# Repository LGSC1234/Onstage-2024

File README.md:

# Onstage-2024
Este repositorio tiene como objetivo demostrar el innovador trabajo del equipo, donde hemos integrado el emocionante tema de Taylor Swift dentro de nuestra performance.

-Robot Principal "Taylor Swift"

-Robot Secundario "Cartel Reconocimiento"

-Robot Secundario "Cartel Seguir Humano"

Para instalar el código de pyton se instalan las librerias mediante el requirements.txt y correr el archivo de main.py con permisos de administrador

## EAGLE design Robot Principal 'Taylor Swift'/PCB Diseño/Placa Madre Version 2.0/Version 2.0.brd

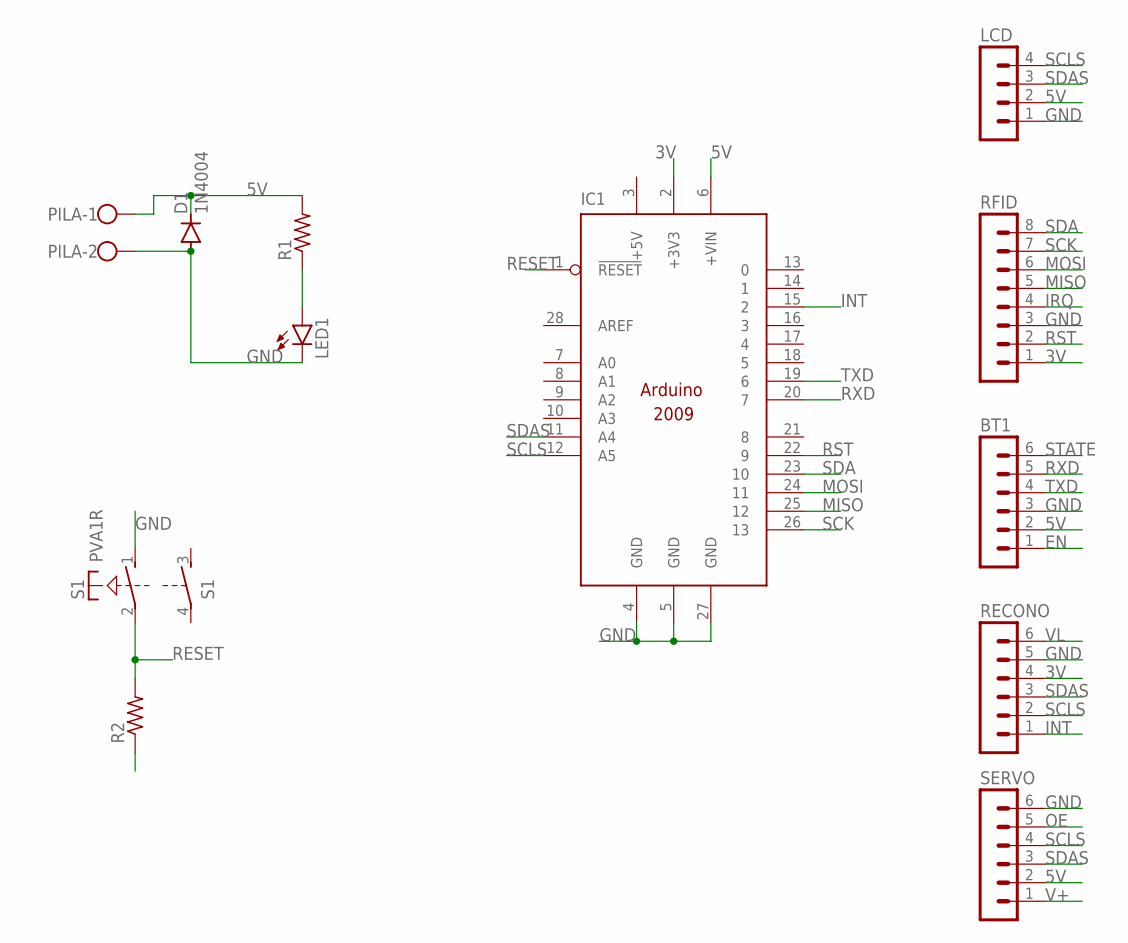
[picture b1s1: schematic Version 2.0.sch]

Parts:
BT1: MA06-1
D1: 1N4004; DO41-10
IC1: ARDUINO2009_10; ARDUINO2009
LCD: MA04-1
LED1: LED3MM
PILA: W237-102
R1, R2: R-US_0204/7; 0204/7
RECONO: MA06-1
RFID: MA08-1
S1: PVA1R
SERVO: MA06-1

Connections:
3V: IC1.2 (+3V3), RECONO.4, RFID.1
5V: BT1.2, D1.C, IC1.6 (+VIN), LCD.2, PILA.1, R1.2, R2.1, SERVO.2
+5V: IC1.3 (+5V)
EN: BT1.1
GND: BT1.3, D1.A, IC1.4 (GND), IC1.5 (GND), IC1.27 (GND), LCD.1, LED1.K (C), PILA.2, RECONO.5, RFID.3, S1.1 (S), SERVO.6
INT: IC1.15 (2), RECONO.1
IRQ: RFID.4
MISO: IC1.25 (12), RFID.5
MOSI: IC1.24 (11), RFID.6
unnamed: LED1.A, R1.1
OE: SERVO.5
RESET: IC1.1 (!RESET), R2.2, S1.2
RST: IC1.22 (9), RFID.2
RXD: BT1.5, IC1.20 (7)
SCK: IC1.26 (13), RFID.7
SCLS: IC1.12 (A5), LCD.4, RECONO.2, SERVO.4
SDA: IC1.23 (10), RFID.8
SDAS: IC1.11 (A4), LCD.3, RECONO.3, SERVO.3
STATE: BT1.6
TXD: BT1.4, IC1.19 (6)
V+: SERVO.1
VL: RECONO.6

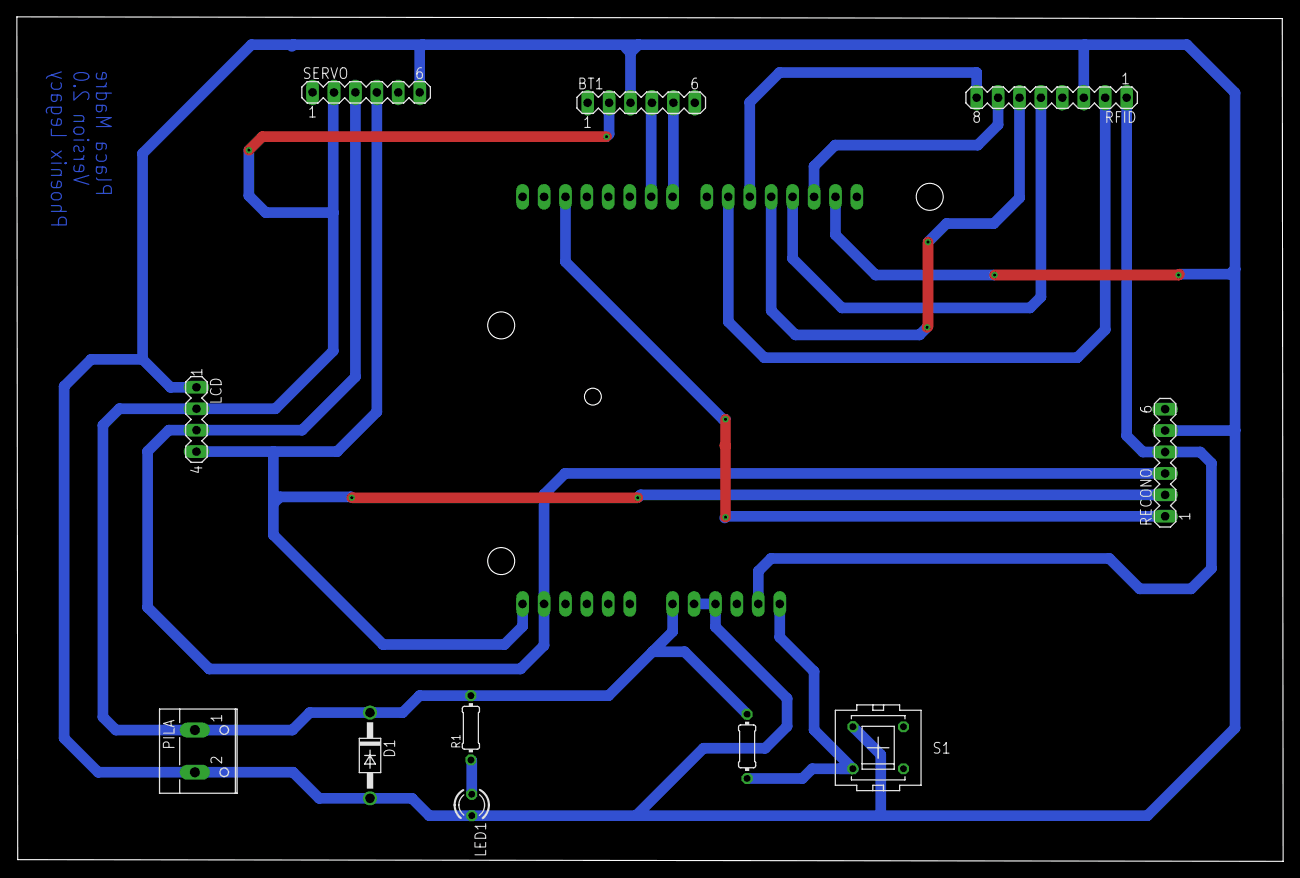
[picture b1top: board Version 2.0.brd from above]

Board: 2 copper layers, 150.1 x 100.1 mm, 12 parts (1 on the bottom side), 15 nets.

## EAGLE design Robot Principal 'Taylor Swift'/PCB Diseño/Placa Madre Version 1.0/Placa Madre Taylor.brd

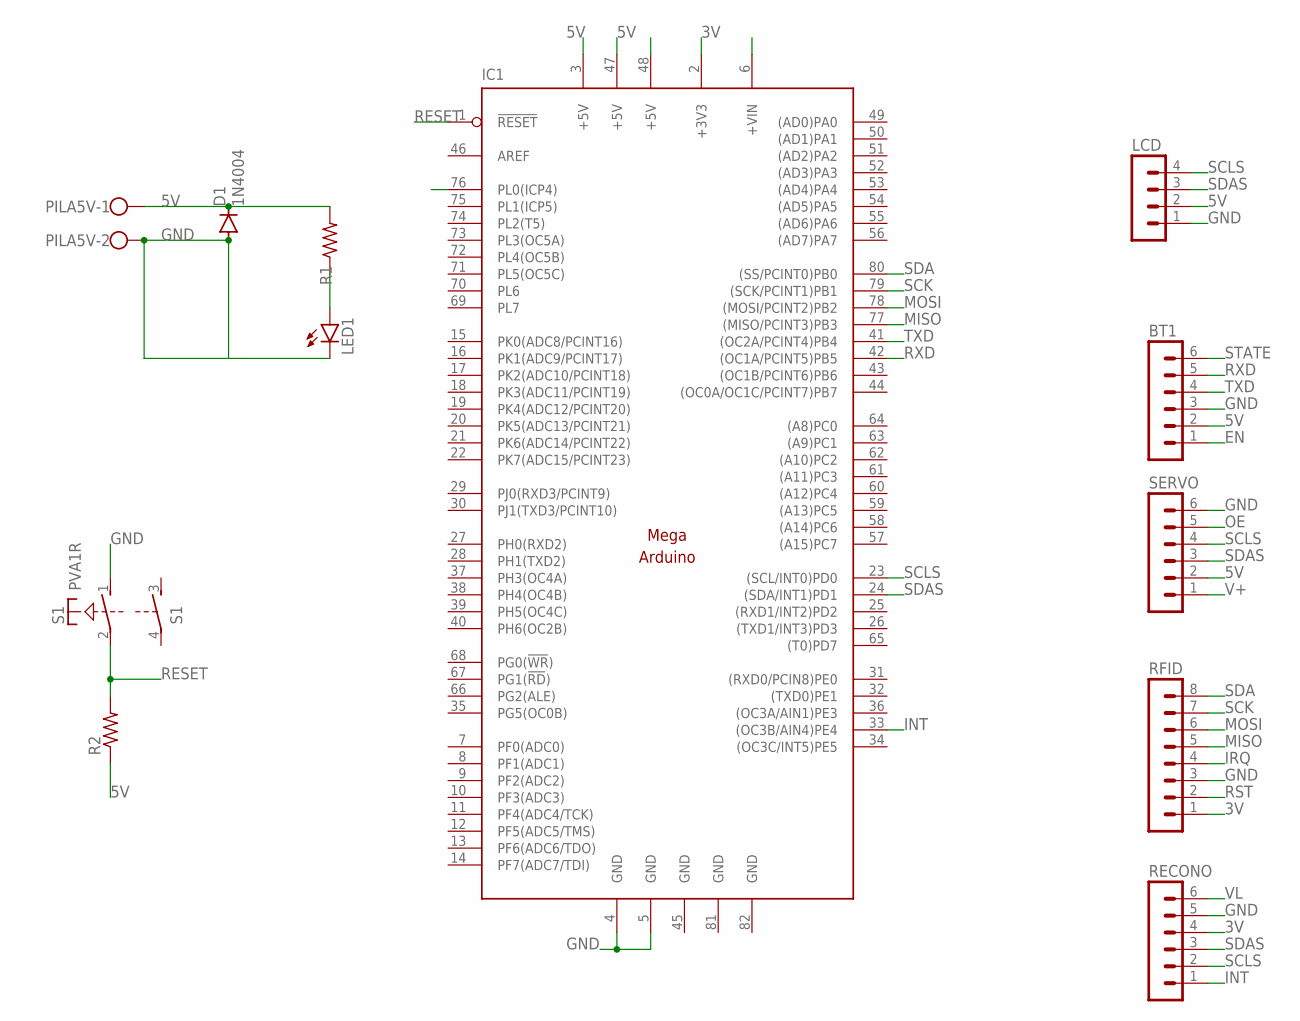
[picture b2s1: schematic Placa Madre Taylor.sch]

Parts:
BT1: MA06-1
D1: 1N4004; DO41-10
IC1: MEGAARDUINO_11; MEGA_ARDUINO_1
LCD: MA04-1
LED1: LED3MM
PILA5V: W237-102
R1: R-US_0204/7; 0204/7
R2: R-US_0207/10; 0207/10
RECONO: MA06-1
RFID: MA08-1
S1: PVA1R
SERVO: MA06-1

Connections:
3V: IC1.2 (+3V3), RECONO.4, RFID.1
5V: BT1.2, D1.C, IC1.3 (+5V), IC1.6 (+VIN), IC1.47 (+5V), LCD.2, PILA5V.1, R1.2, R2.1, SERVO.2
EN: BT1.1
GND: BT1.3, D1.A, IC1.4 (GND), IC1.5 (GND), IC1.45 (GND), IC1.81 (GND), IC1.82 (GND), LCD.1, LED1.K (C), PILA5V.2, RECONO.5, RFID.3, S1.1 (S), SERVO.6
INT: IC1.33 ((OC3B/AIN4)PE4), RECONO.1
IRQ: RFID.4
MISO: IC1.77 ((MISO/PCINT3)PB3), RFID.5
MOSI: IC1.78 ((MOSI/PCINT2)PB2), RFID.6
unnamed: LED1.A, R1.1
OE: SERVO.5
RESET: IC1.1 (!RESET), R2.2, S1.2
RST: IC1.76 (PL0(ICP4)), RFID.2
RXD: BT1.5, IC1.42 ((OC1A/PCINT5)PB5)
SCK: IC1.79 ((SCK/PCINT1)PB1), RFID.7
SCLS: IC1.23 ((SCL/INT0)PD0), LCD.4, RECONO.2, SERVO.4
SDA: IC1.80 ((SS/PCINT0)PB0), RFID.8
SDAS: IC1.24 ((SDA/INT1)PD1), LCD.3, RECONO.3, SERVO.3
STATE: BT1.6
TXD: BT1.4, IC1.41 ((OC2A/PCINT4)PB4)
V+: SERVO.1
VL: RECONO.6

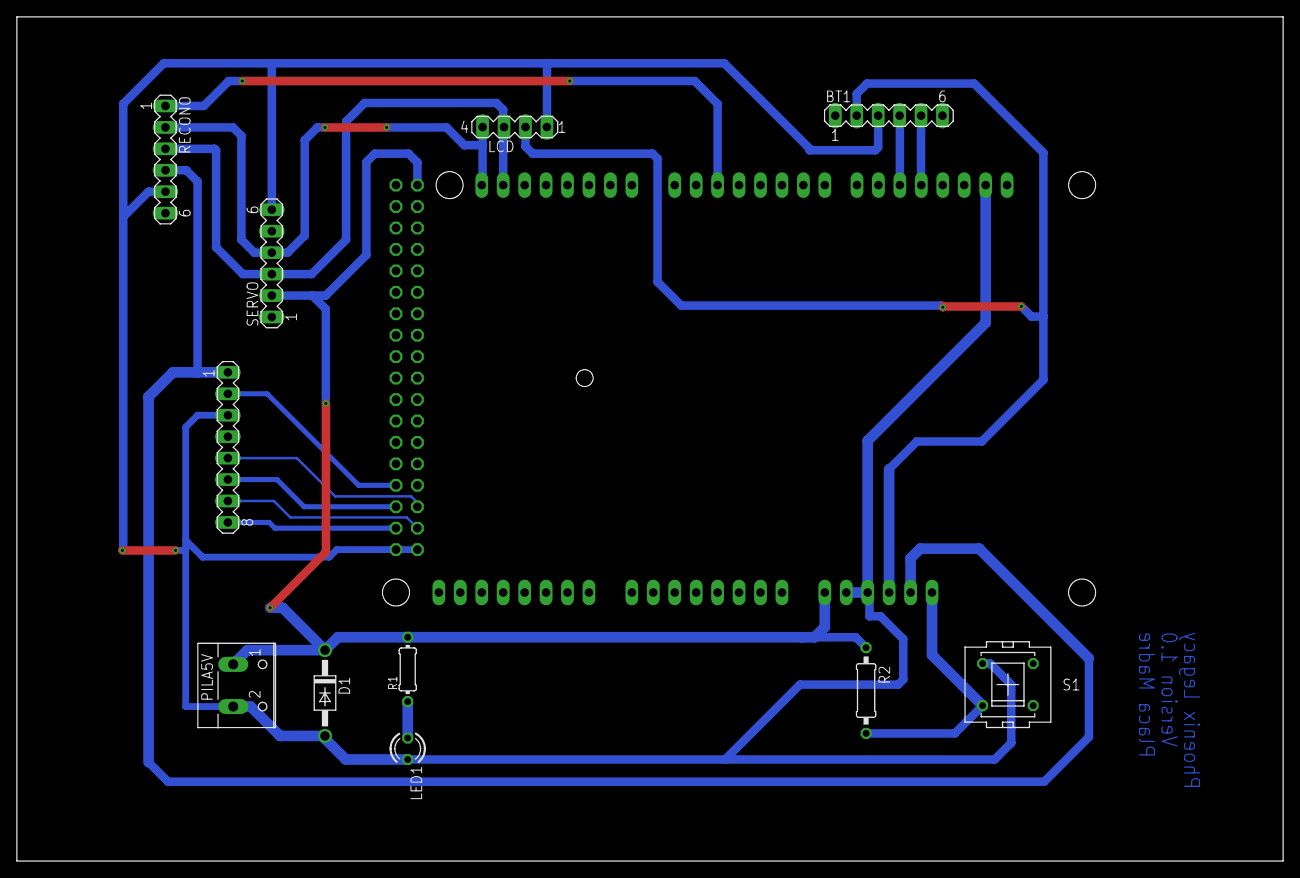
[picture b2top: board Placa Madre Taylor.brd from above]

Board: 2 copper layers, 150.0 x 100.0 mm, 12 parts (1 on the bottom side), 15 nets.

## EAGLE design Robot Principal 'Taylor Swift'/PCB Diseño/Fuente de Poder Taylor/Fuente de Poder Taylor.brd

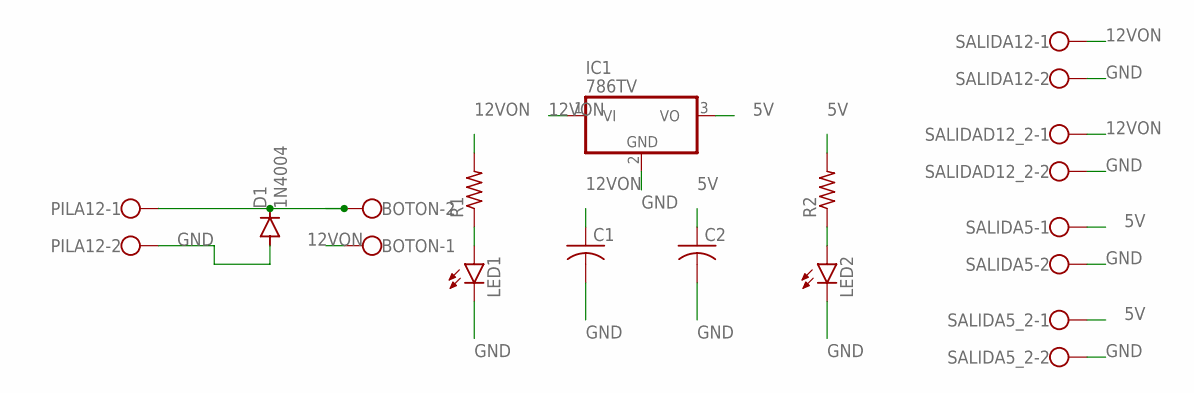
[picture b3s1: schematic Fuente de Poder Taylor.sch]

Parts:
BOTON: W237-102
C1, C2: C-US025-024X044; C025-024X044
D1: 1N4004; DO41-10
IC1: 786TV; TO220V
LED1, LED2: LED3MM
PILA12: W237-102
R1, R2: R-US_0204/7; 0204/7
SALIDA5, SALIDA5_2, SALIDA12: W237-102
SALIDAD12_2: W237-102

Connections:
5V: C2.1, IC1.3 (VO), R2.2, SALIDA5.1, SALIDA5_2.1
12VIN: BOTON.2, D1.C, PILA12.1
12VON: BOTON.1, C1.1, IC1.1 (VI), R1.2, SALIDA12.1, SALIDAD12_2.1
GND: C1.2, C2.2, D1.A, IC1.2 (GND), LED1.K (C), LED2.K (C), PILA12.2, SALIDA5.2, SALIDA5_2.2, SALIDA12.2, SALIDAD12_2.2
unnamed: LED1.A, R1.1
unnamed: LED2.A, R2.1

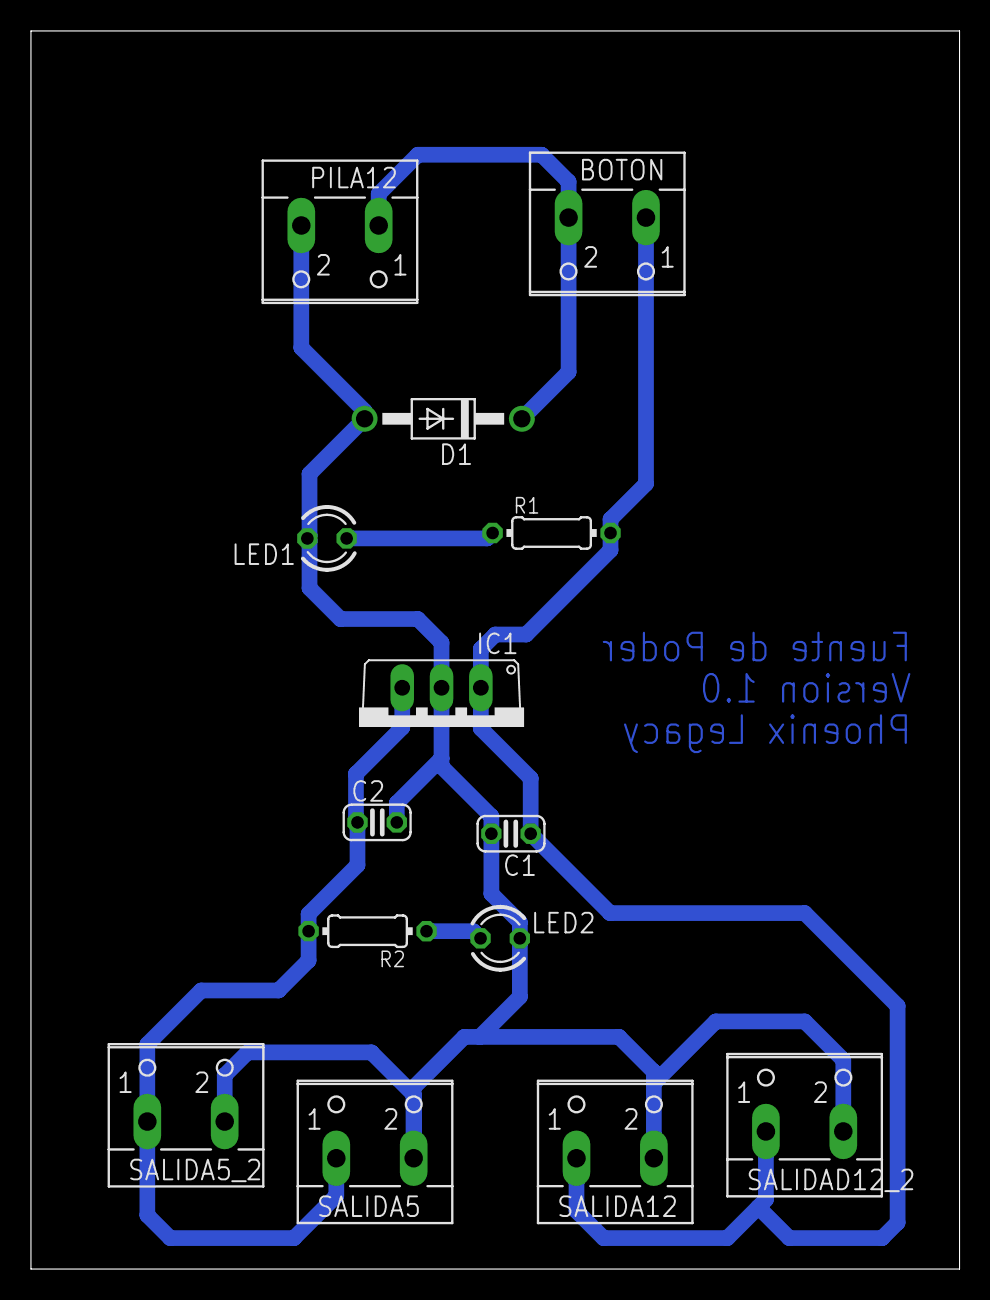
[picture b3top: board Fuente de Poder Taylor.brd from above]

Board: 2 copper layers, 60.0 x 80.0 mm, 14 parts (0 on the bottom side), 6 nets.

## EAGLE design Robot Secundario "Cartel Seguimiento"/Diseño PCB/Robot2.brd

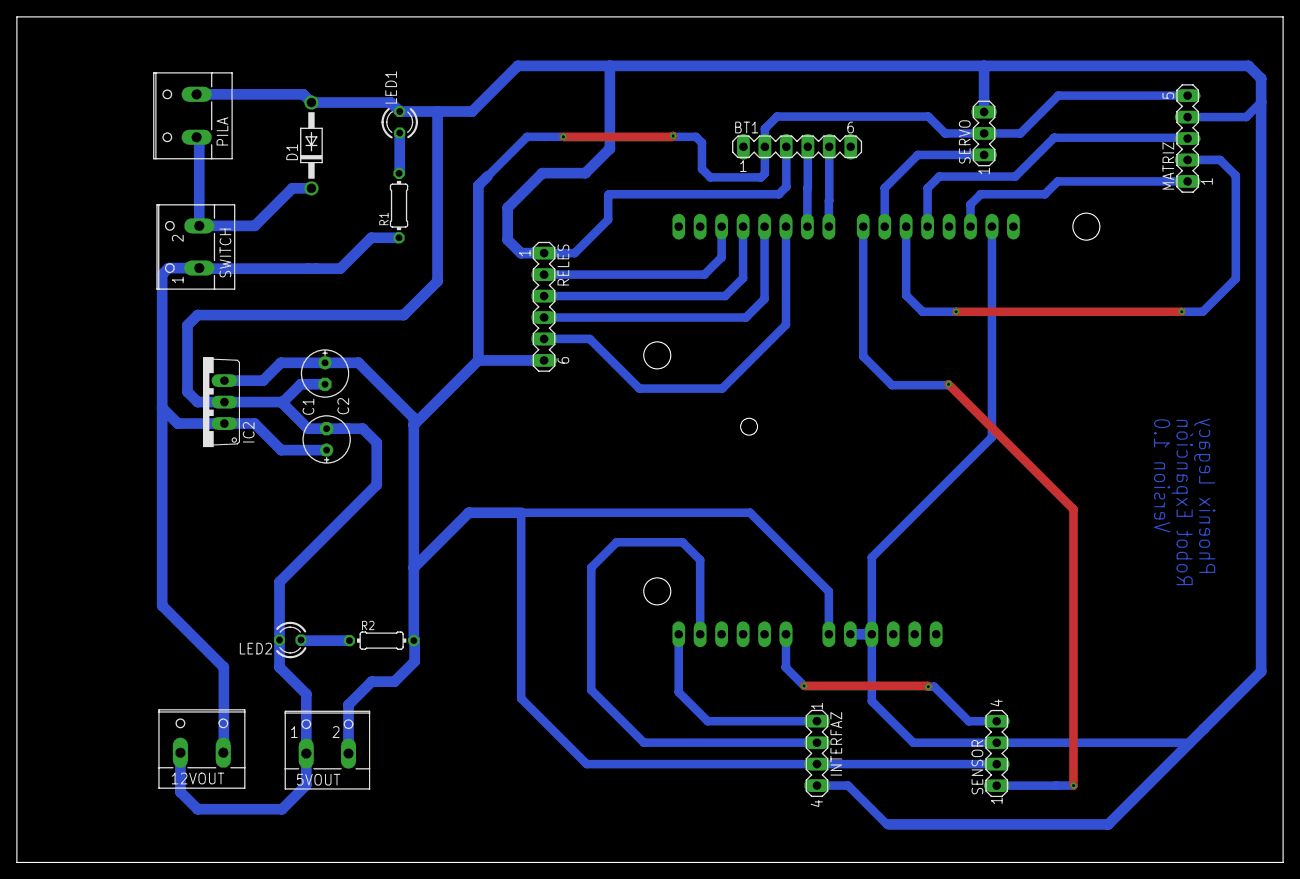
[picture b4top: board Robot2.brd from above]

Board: 2 copper layers, 149.9 x 100.1 mm, 19 parts (1 on the bottom side), 20 nets.

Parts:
5VOUT: W237-102
12VOUT: W237-132
BT1: MA06-1
C1, C2: E2,5-6E
D1: 1N4004; DO41-10
IC1: ARDUINO2009_1
IC2: 786TV; TO220V
INTERFAZ: MA04-1
LED1, LED2: LED3MM
MATRIZ: MA05-1
PILA: W237-132
R1, R2: 0204/7
RELES: MA06-1
SENSOR: MA04-1
SERVO: MA03-1
SWITCH: W237-102

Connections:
5V: 5VOUT.2, BT1.2, C2.+, IC1.6, IC2.3, INTERFAZ.3, MATRIZ.5, R2.2, RELES.6, SENSOR.2, SERVO.2
12VIN: D1.C, PILA.1, SWITCH.2
12VON: 12VOUT.2, C1.+, IC2.1, R1.1, SWITCH.1
A0: IC1.7, SENSOR.4
CLK: IC1.26, MATRIZ.1
CS: IC1.23, MATRIZ.2
D8: IC1.21, SENSOR.1
D9: IC1.22, SERVO.1
DIN: IC1.24, MATRIZ.3
GND: 5VOUT.1, 12VOUT.1, BT1.3, C1.-, C2.-, D1.A, IC1.4, IC1.5, IC1.27, IC2.2, INTERFAZ.4, LED1.K, LED2.K, MATRIZ.4, PILA.2, RELES.1, SENSOR.3, SERVO.3
IN1: IC1.15, RELES.2
IN2: IC1.16, RELES.3
IN3: IC1.17, RELES.4
IN4: IC1.18, RELES.5
unnamed: LED1.A, R1.2
unnamed: LED2.A, R2.1
RXD: BT1.5, IC1.20
SCL: IC1.12, INTERFAZ.1
SDA: IC1.11, INTERFAZ.2
TXD: BT1.4, IC1.19

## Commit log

2024-04-14 Create Robot Taylor Swift
    Presentamos a u nuestro robot principal "Taylor Switf"
2024-04-14 Codigo
2024-04-14 Create PCB
2024-04-14 Create Fuente
2024-04-15 Create Librerias Arduino
2024-04-15 Create Matriz Libreria
2024-04-15 Create docs
2024-04-15 Create Search
2024-04-15 Create Codigo
2024-04-15 Create Python
2024-04-15 Create Reconocimiento
2024-04-15 Create código
2024-04-15 Create venv
2024-04-15 Create delete ven
2024-04-16 Rename main.py to test3.py
2024-04-16 Rename test2.py to main.py
2024-04-16 Add files via upload
    adding the requirement.txt file
2024-04-18 Update main.py
    comentarios del código
2024-04-18 Update main.py
    comentarios agregados
2024-04-18 Create Poster
2024-04-18 Create Video
2024-04-18 Rename Video to Link
2024-04-18 Update Link
2024-04-18 Create Material Usado
